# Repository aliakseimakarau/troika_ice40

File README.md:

This is an implementation of the Troika hashing algorithmus on ICE40 FPGAs.

The repository is intended to be used by developers who are considering using Troika in their hardware projects. The board-files are from a PoC which can be used as design example.

It's not a high-performance solution because it needs multiple clock-cycles per hash-round and the implementation is heavily restricted by logic resources and achievable speed of ICE40 FPGAs. But the FPGA is very cheap, the PCB can be done by any cheap chinese manufacturer and soldering is doable with a bit of practice. And it's a lot faster than doing hash calculations only in software if using e.g. auto-padding and/or multi-hash-loops. IOTA library functions can benefit much because 1. it works much with 243Trit vectors and 2. they often do multiple hashing loops (e.g. address generation, signing).

Support for this repository is limited because it's just a PoC and intended for experienced developers. (by the way, it's the same PCB as for the PoWChip PoC - for Troika the GSM/BT/GPS modul is not needed and software for it is not included in the repository).

Some features (FPGA):
- ICE40UP5K ($5 FPGA in QFN package)
- FPGA about 73% utilized
- running at 36MHz (uses internal 48MHz oscillator + PLL; no external oscillator required)
- Data-transfers via SPI
- It needs 55 clock cycles per hash
- It can do auto-padding for 243Trit input size (single Block; in IOTA used a lot)
- It can do multiple loops with auto-padding (this is interesting for e.g. IOTA where often a block has to be hashed multiple times; It reduces transfer-times significantly)
- It supports nested hashing by "push"ing" and "pop"ing the internal Troika state to and from a "Stack" (actually, it's an internal offset for RAM address but it acts like a stack).

PCB:
- ICE40UP5K FPGA
- STM32F302CCTx µC (default DFU Bootloader can be used)
- Pinheader for GSM/GPS/BT module (not used in this application)
- Some LEDs, Buttons
- SWD Debug header

Performance:
- 10k blocks (including SPI transfer times) in 11.6s
- 1k blocks with 27 hash-loops (including SPI transfer times and auto-padding) in 2.6s

This repository contains:
- Radiant project files for ICE40 FPGAs with VHDL source files
- Example Board-Design
- Eclipse project with code for STM32F302

Just a small note ... A synthesized ICE40 Bitstream is included in the STM32-code (bitstream.h)

License (MIT):
```
-- 2018 by Thomas Pototschnig <microengineer18@gmail.com,
-- http://microengineer.eu
-- discord: pmaxuw#8292
-- donations-address: 
--     LLEYMHRKXWSPMGCMZFPKKTHSEMYJTNAZXSAYZGQUEXLXEEWPXUNWBFDWESOJVLHQHXOPQEYXGIRBYTLRWHMJAOSHUY
-- 
-- Permission is hereby granted, free of charge, to any person obtaining
-- a copy of this software and associated documentation files (the
-- "Software"), to deal in the Software without restriction, including
-- without limitation the rights to use, copy, modify, merge, publish,
-- distribute, sublicense, and/or sell copies of the Software, and to
-- permit persons to whom the Software is furnished to do so, subject to
-- the following conditions:
-- 
-- The above copyright notice and this permission notice shall be
-- included in all copies or substantial portions of the Software.
-- 
-- THE SOFTWARE IS PROVIDED "AS IS", WITHOUT WARRANTY OF ANY KIND,
-- EXPRESS OR IMPLIED, INCLUDING BUT NOT LIMITED TO THE WARRANTIES OF
-- MERCHANTABILITY, FITNESS FOR A PARTICULAR PURPOSE AND
-- NONINFRINGEMENT. IN NO EVENT SHALL THE AUTHORS OR COPYRIGHT HOLDERS BE
-- LIABLE FOR ANY CLAIM, DAMAGES OR OTHER LIABILITY, WHETHER IN AN ACTION
-- OF CONTRACT, TORT OR OTHERWISE, ARISING FROM, OUT OF OR IN CONNECTION
-- WITH THE SOFTWARE OR THE USE OR OTHER DEALINGS IN THE SOFTWAR
```

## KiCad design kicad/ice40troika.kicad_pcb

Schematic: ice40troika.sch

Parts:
C1, C2, C10, C11, C32, C34, C35: 1µ; C_0603_1608Metric
C3, C36: 10µ; C_0603_1608Metric
C4, C5, C6, C7, C12, C13, C16, C19, C20, C24, C25, C26, C27, C31, C33: 100n; C_0603_1608Metric
C8, C9, C14, C15, C18: 10n; C_0603_1608Metric
C17, C28, C29, C30: 47µ; C_1210_3225Metric
C21: 4.7µ/X5R; C_1206_3216Metric
C22, C23: 47p; C_0603_1608Metric
D1: D; D_SOD-523
D2, D3: LED; LED_0603_1608Metric
JP1: Jumper_NC_Dual; SolderJumper-3_P1.3mm_Open_RoundedPad1.0x1.5mm
P1: 10104110-0001LF; MICROUSBB
P2: CONN_01X05; PinHeader_1x05_P1.27mm_Vertical
R1, R2, R4, R6, R7, R9, R12, R18, R19, R22: 10k; R_0603_1608Metric
R3: 100; R_0603_1608Metric
R5: 100k; R_0603_1608Metric
R8, R11, R13, R20: 22; R_0603_1608Metric
R10: 1k5; R_0603_1608Metric
R14, R21: 270; R_0603_1608Metric
R15: 1; R_1210_3225Metric
R16, R17: 33; R_0603_1608Metric
SW1, SW2, SW3: KMR2; SW_SPST_KMR2
U1: ice40up5k; ice40up-QFN-48
U3: USBLC6-2SC6; SOT-23-6
U4: STM32F302CCT6; LQFP-48_7x7mm_P0.5mm
U5: SIM808
U6: LP2985-3.3; SOT-23-5
U7: MIC5504-1.2YM5; SOT-23-5
X1: 8MHz; Oscillator_SMD_Abracon_ASE-4Pin_3.2x2.5mm

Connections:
+1V2: C2.1, C6.1, C9.1, C31.1, R3.2, R15.1, U1.5, U1.30
+3V3: C1.1, C4.2, C5.1, C8.1, C10.1, C11.1, C12.1, C13.1, C14.1, C15.1, C16.1, C24.1, C25.1, C26.1, C27.1, C34.1, C36.1, D1.2, R1.2, R2.2, R4.2, R6.2, R9.1, R10.2, R14.1, R21.1, SW2.1, SW3.1, U1.1, U1.22, U1.33, U4.9, U4.24, U4.36, U4.48, U6.5 (VOUT), U7.1 (VIN), U7.3 (EN), X1.4
/CDONE: R4.1, U1.7, U4.11
/CLK_OUT: R20.2, U1.35
/CRESET_B: R2.1, U1.8, U4.10
/D+: R10.1, R17.2, U3.1
/D-: R16.2, U3.3
/GSM_PWRKEY: U4.19, U5.K
/GSM_RXD: U4.12, U5.R
/GSM_SLEEP: U4.18, U5.S
/GSM_TXD: U4.13, U5.T
/LED_FOUND: D2.1, U1.2
/LED_OVERFLOW: U1.3
/LED_RUNNING: U1.4
/PLL_HOLD: R19.2, U1.34, U4.30
/POW_MISO: U1.46, U4.16
/POW_MOSI: U1.45, U4.17
/POW_RESET: U1.47
/POW_SCK: U1.44, U4.15
/POW_SS: U1.48, U4.14
/SPI_MISO: U1.14, U4.27
/SPI_MOSI: U1.17, U4.28
/SPI_SCK: R1.1, R11.2, U1.15
/SPI_SS: JP1.2, U1.16, U4.25
/SWCLK: P2.4, U4.37
/SWDIO: P2.3, U4.34
/SWITCH: R18.1, SW3.2
/USB_D+: C23.2, R17.1, U4.33
/USB_D-: C22.2, R16.1, U4.32
/spare1: U1.36, U4.22
/spare2: R13.2, U1.37
/spare3: U1.38, U4.20
ARM_NRST: C20.1, P2.2, R9.2, SW1.2, U4.7
GND: C1.2, C2.2, C3.2, C4.1, C5.2, C6.2, C7.2, C8.2, C9.2, C10.2, C11.2, C12.2, C13.2, C14.2, C15.2, C16.2, C17.2, C18.1, C19.1, C20.2, C21.1, C22.1, C23.1, C24.2, C25.2, C26.2, C27.2, C28.2, C29.2, C30.2, C31.2, C32.2, C33.1, C34.2, C35.2, C36.2, P1.5, P1.6, P2.5, R5.2, R7.1, R12.2, R18.2, R19.1, R22.2, SW1.1, U1.49, U3.2, U4.8, U4.23, U4.35, U4.47, U5.G, U6.2 (GND), U7.2 (GND), X1.2
unnamed: C3.1, C7.1, R3.1, U1.29
unnamed: C33.2, U6.4 (BP)
unnamed: C35.1, R15.2, U7.5 (VOUT)
unnamed: D1.1, U1.24
unnamed: D2.2, R14.2
unnamed: D3.1, U4.41
unnamed: D3.2, R21.2
unnamed: JP1.1, R6.1
unnamed: JP1.3, R7.2
unnamed: P1.2, U3.4
unnamed: P1.3, U3.6
unnamed: P1.4, R5.1
unnamed: R8.1, U4.5
unnamed: R8.2, X1.3
unnamed: R11.1, U4.26
unnamed: R12.1, SW2.2, U4.44
unnamed: R13.1, U4.21
unnamed: R20.1, U4.29
unnamed: R22.1, U4.46, X1.1
POWER_USB: C17.1, C18.2, C19.2, C21.2, C28.1, C29.1, C30.1, C32.1, P1.1, U3.5, U5.V, U6.1 (VIN), U6.3 (ON/~OFF~)

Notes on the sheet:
LO = Boot from flash

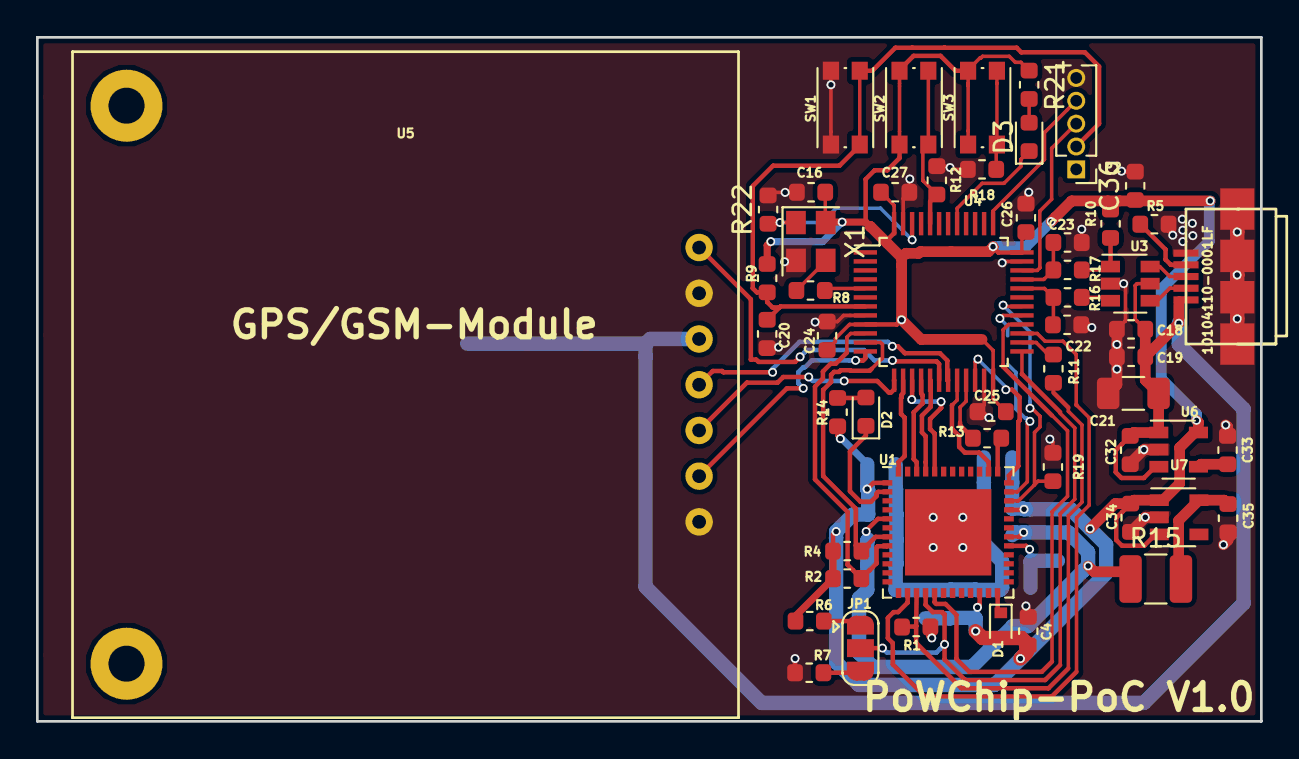
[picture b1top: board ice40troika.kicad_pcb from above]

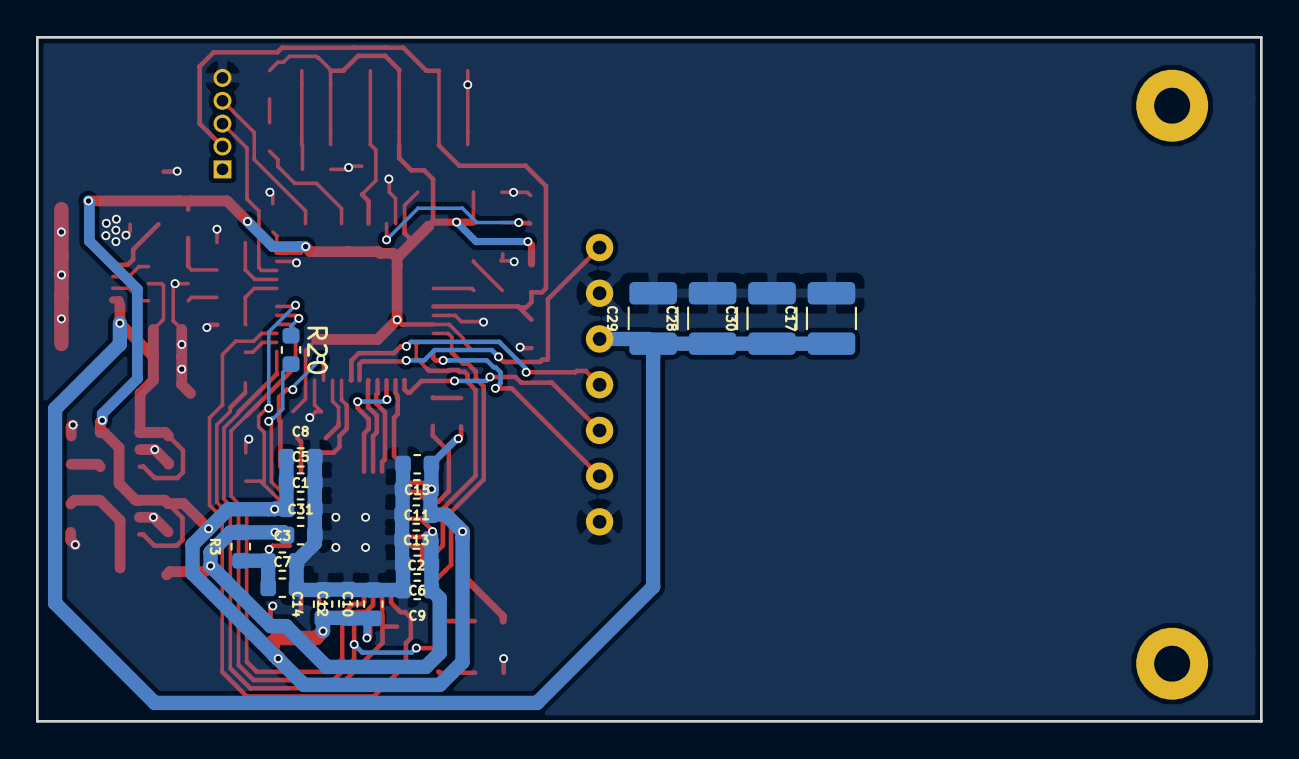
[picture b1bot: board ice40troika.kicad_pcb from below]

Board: 2 copper layers, 68.0 x 38.0 mm, 74 parts (21 on the bottom side), 51 nets.

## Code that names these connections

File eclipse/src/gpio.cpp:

/*
-- Troika for ICE40-FPGA
--
-- 2018 by Thomas Pototschnig <microengineer18@gmail.com,
-- http://microengineer.eu
-- discord: pmaxuw#8292
-- donations-address:
--     LLEYMHRKXWSPMGCMZFPKKTHSEMYJTNAZXSAYZGQUEXLXEEWPXUNWBFDWESOJVLHQHXOPQEYXGIRBYTLRWHMJAOSHUY
--
-- Permission is hereby granted, free of charge, to any person obtaining
-- a copy of this software and associated documentation files (the
-- "Software"), to deal in the Software without restriction, including
-- without limitation the rights to use, copy, modify, merge, publish,
-- distribute, sublicense, and/or sell copies of the Software, and to
-- permit persons to whom the Software is furnished to do so, subject to
-- the following conditions:
--
-- The above copyright notice and this permission notice shall be
-- included in all copies or substantial portions of the Software.
--
-- THE SOFTWARE IS PROVIDED "AS IS", WITHOUT WARRANTY OF ANY KIND,
-- EXPRESS OR IMPLIED, INCLUDING BUT NOT LIMITED TO THE WARRANTIES OF
-- MERCHANTABILITY, FITNESS FOR A PARTICULAR PURPOSE AND
-- NONINFRINGEMENT. IN NO EVENT SHALL THE AUTHORS OR COPYRIGHT HOLDERS BE
-- LIABLE FOR ANY CLAIM, DAMAGES OR OTHER LIABILITY, WHETHER IN AN ACTION
-- OF CONTRACT, TORT OR OTHERWISE, ARISING FROM, OUT OF OR IN CONNECTION
-- WITH THE SOFTWARE OR THE USE OR OTHER DEALINGS IN THE SOFTWAR
*/

#include "gpio.h"
#include "stm32f30x_gpio.h"


#define GPIOA_LED		GPIO_Pin_0



//#define SPI_GPIO      GPIOB
#define GPIOA_MOSI  GPIO_Pin_7
#define GPIOA_MISO  GPIO_Pin_6
#define GPIOA_SCK  	GPIO_Pin_5
#define GPIOA_SS   	GPIO_Pin_3

#define GPIOB_nSTATUS	GPIO_Pin_4
#define GPIOB_DCK		GPIO_Pin_7
#define GPIOB_DATA0		GPIO_Pin_8
#define GPIOB_nCONFIG	GPIO_Pin_9
#define GPIOA_CONFDONE	GPIO_Pin_2
#define GPIOA_PIDETECT	GPIO_Pin_15

#define GPIOB_DISC		GPIO_Pin_2


#define GPIOB_GSM_SLEEP		GPIO_Pin_0
#define GPIOB_GSM_PWRKEY	GPIO_Pin_1

#define GPIOB_CONF_SS		GPIO_Pin_12
#define GPIOB_CONF_SCK		GPIO_Pin_13
#define GPIOB_CONF_MISO		GPIO_Pin_14
#define GPIOB_CONF_MOSI		GPIO_Pin_15

#define GPIOA_CRESET_B		GPIO_Pin_0
#define GPIOA_CDONE			GPIO_Pin_1
#define GPIOA_GSM_RXD		GPIO_Pin_2
#define GPIOA_GSM_TXD		GPIO_Pin_3
#define GPIOA_POW_SS		GPIO_Pin_4
#define GPIOA_POW_SCK		GPIO_Pin_5
#define GPIOA_POW_MISO		GPIO_Pin_6
#define GPIOA_POW_MOSI		GPIO_Pin_7
#define GPIOA_CLK_OUT		GPIO_Pin_8
#define GPIOA_PLL_HOLD		GPIO_Pin_9


/*
#define SPI_CONF_RCC	RCC_APB1Periph_SPI2
#define SPI_CONF		SPI2
#define SPI_GPIO_RCC	RCC_APB2Periph_GPIOB

#define SPI_POW_RCC		RCC_APB1Perip_SPI1
#define SPI_POW			SPI1
#define SPI_GPIO_RCC	RCC_APB2Periph_GPIOA
*/

void GPIOClass::set(GPIOPin* g) {
	GPIO_WriteBit(g->getGPIO(), g->getPinNr(), Bit_SET);
}

void GPIOClass::clr(GPIOPin* g) {
	GPIO_WriteBit(g->getGPIO(), g->getPinNr(), Bit_RESET);
}

void GPIOClass::set(PinsEnum e) {
	set(getGPIOPin(e));
}

void GPIOClass::clr(PinsEnum e) {
	clr(getGPIOPin(e));
}

GPIOPin* GPIOClass::getGPIOPin(PinsEnum e) {
	return Pins[e];
}

BitAction GPIOClass::read(GPIOPin* g) {
	return GPIO_ReadInputDataBit(g->getGPIO(), g->getPinNr()) ? Bit_SET : Bit_RESET;
}

BitAction GPIOClass::read(PinsEnum e) {
	return read(getGPIOPin(e));
}


GPIOClass::GPIOClass() {

//	Pins[PinsEnum::GSM_SLEEP] = new GPIOPinOut(GPIOB, GPIOB_GSM_SLEEP, Bit_SET);
//	Pins[PinsEnum::GSM_PWRKEY] = new GPIOPinOut(GPIOB, GPIOB_GSM_PWRKEY, Bit_SET);

	Pins[PinsEnum::CRESET_B] = new GPIOPinOut(GPIOA, GPIOA_CRESET_B, Bit_RESET);	// reset FPGA
	Pins[PinsEnum::CDONE] = new GPIOPinIn(GPIOA, GPIOA_CDONE, GPIO_PuPd_NOPULL);

	Pins[PinsEnum::CONF_SS] = new GPIOPinOut(GPIOB, GPIOB_CONF_SS, Bit_RESET);		// low = configure as spi slave
	Pins[PinsEnum::CONF_SCK] = new GPIOPinOut(GPIOB, GPIOB_CONF_SCK, Bit_RESET);
	Pins[PinsEnum::CONF_MOSI] = new GPIOPinOut(GPIOB, GPIOB_CONF_MOSI, Bit_RESET);
	Pins[PinsEnum::CONF_MISO] = new GPIOPinIn(GPIOB, GPIOB_CONF_MISO, GPIO_PuPd_NOPULL);

	Pins[PinsEnum::LED] = new GPIOPinOut(GPIOB, GPIOB_LED, Bit_SET);

	Pins[PinsEnum::HSE_EN] = new GPIOPinOut(GPIOB, GPIOB_HSE_EN, Bit_SET);

//	Pins[PinsEnum::GSM_TXD] = new GPIOPinIn(GPIOA, GPIOA_GSM_TXD, GPIO_PuPd_NOPULL);
//	Pins[PinsEnum::GSM_RXD] = new GPIOPinOut(GPIOA, GPIOA_GSM_RXD, Bit_SET);

	Pins[PinsEnum::POW_SS] = new GPIOPinOut(GPIOA, GPIOA_POW_SS, Bit_SET);
/*	Pins[PinsEnum::POW_SCK] = new GPIOPinAF(GPIOA, GPIOA_POW_SCK, Bit_RESET);
	Pins[PinsEnum::POW_MOSI] = new GPIOPinAF(GPIOA, GPIOA_POW_MOSI, Bit_RESET);
	Pins[PinsEnum::POW_MISO] = new GPIOPinAF(GPIOA, GPIOA_POW_MISO, GPIO_PuPd_NOPULL, Bit_SET);*/

	Pins[PinsEnum::PLL_HOLD] = new GPIOPinOut(GPIOA, GPIOA_PLL_HOLD, Bit_RESET);
//	Pins[PinsEnum::CLK_OUT] = new GPIOPinOut(GPIOA, GPIOA_CLK_OUT, Bit_RESET);
}



void GPIOClass::init() {
	GPIO_InitTypeDef GPIO_InitStruct;
RCC_AHBPeriphClockCmd(RCC_AHBPeriph_GPIOA, ENABLE);
	RCC_AHBPeriphClockCmd(RCC_AHBPeriph_GPIOB, ENABLE);
	RCC_AHBPeriphClockCmd(RCC_AHBPeriph_GPIOC, ENABLE);
	RCC_APB1PeriphClockCmd(RCC_APB1Periph_SPI2, ENABLE);
	for (int i=0;i<PinsEnum::NUM_ELEMENTS;i++) {
		if (!Pins[i])
			continue;

		if (Pins[i]->getInitValue() == Bit_SET) {
			set(Pins[i]);
		} else
			clr(Pins[i]);
	}

	GPIO_InitStruct.GPIO_Speed = GPIO_Speed_50MHz;
	for (int i=0;i<PinsEnum::NUM_ELEMENTS;i++) {
		if (!Pins[i])
			continue;
		GPIO_InitStruct.GPIO_Pin = Pins[i]->getPinNr();
		GPIO_InitStruct.GPIO_Mode = Pins[i]->getType();
		GPIO_InitStruct.GPIO_OType = Pins[i]->getOType();
		GPIO_InitStruct.GPIO_PuPd = Pins[i]->getPUP();
		GPIO_Init(Pins[i]->getGPIO(), &GPIO_InitStruct);
	}

}

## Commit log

2019-01-29 renamed powchip to ice40troika
2019-01-29 changed readme; forgot to git add files
2019-01-29 eclipse project and kicad schematic added
2019-01-29 README moved and changed
2019-01-29 header added
2019-01-29 license included
